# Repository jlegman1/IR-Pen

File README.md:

## Disclaimer
This project is intended for educational and research purposes only. It should be used responsibly and only in environments where you have permission to transmit infrared signals.
##
I created a PCB created that sends IR signals to TVs. You click a button and it uses TV-B-Gone firmware to cycle through all IR signals until a TV turns off. A custom 3d printed shell goes around it hiding the pcb. All kicad files and 3d print files linked. I had created this project because I was playing around with my flipper zero and thought how funny it was to when I turned the tv off when my dad was watching. It gave me motiavtion to create something of my own, so which i did. Overall I hope you enjoy playing around with my desgin!
PCB fits through my 3d printed shell and should fit there tightly but shouldn't fall out. Its diamater is 13mm and its 133mm in height. The PCB is 11mm x 65mm.
##
Firmware created by Mitch Altman and adafruit [TV-B-Gone](https://github.com/adafruit/TV-B-Gone-kit)
## Parts List

- **10440 Lithium Battery 3.7V** — power source that slides into pen body — [Amazon](https://www.amazon.com/dp/B0H1LNY5LW)
- **USBasp Programmer** — for flashing firmware via ISP pads — [Amazon](https://rb.gy/d68i6x)
- **Tactile Button** — trigger to fire IR codes — [DigiKey](https://www.digikey.com/en/products/detail/c-k/PTS526SM15SMTR2-LFS/10056625)
- **10µF Capacitor** — handles big voltage dips — [DigiKey](https://www.digikey.com/en/products/detail/murata-electronics/GRM155R60J106ME05D/11500166)
- **100nF Capacitor** — smooths out voltage spikes — [DigiKey](https://www.digikey.com/en/products/detail/murata-electronics/GRM155R61A104KA01D/587212?s=N4IgTCBcDaIOICUCyBGArGhA2FBBFADACwDSuBKAIiALoC%2BQA)
- **33Ω Resistor** — limits current to IR LED — [DigiKey](https://www.digikey.com/en/products/detail/yageo/RC0402JR-0733RL/726467)
- **3.3kΩ Resistor** — keeps charging at 300mA — [DigiKey](https://www.digikey.com/en/products/detail/panasonic-industry/ERA-2AEB332X/1706017)
- **10kΩ Resistors x2** — keeps ATtiny RESET and button pin stable — [DigiKey](https://www.digikey.com/en/products/detail/stackpole-electronics-inc/RMCF0402FT10K0/1761433)
- **USB-C Connector** — charges the battery — [DigiKey](https://www.digikey.com/en/products/detail/gct/USB4085-GF-A/9859662?s=N4IgTCBcDaIOIGEAqACAqgZQEIBYAMAHAKwgC6AvkA)
- **2N7002 MOSFET** — switch that drives the IR LED — [DigiKey](https://www.digikey.com/en/products/detail/onsemi/2N7002ET1G/1792136)
- **Keystone 5223** — battery spring contact — [DigiKey](https://www.digikey.com/en/products/detail/keystone-electronics/5223/316374)
- **TSAL6400** — IR LED — [DigiKey](https://www.digikey.com/en/products/detail/vishay-semiconductor-opto-division/TSAL6400/1681340)
- **MCP73831T** — battery charger IC — [DigiKey](https://www.digikey.com/en/products/detail/microchip-technology/MCP73831T-2ATI-OT/964303?s=N4IgTCBcDaILIGEAKB2AzADjQRgCoFowBBXASQHoB5XEAXQF8g)
- **ATtiny85-20SU** — main microcontroller — [DigiKey](https://www.digikey.com/en/products/detail/microchip-technology/ATTINY85-20SU/735470)
- Downloadable CSV up top
##

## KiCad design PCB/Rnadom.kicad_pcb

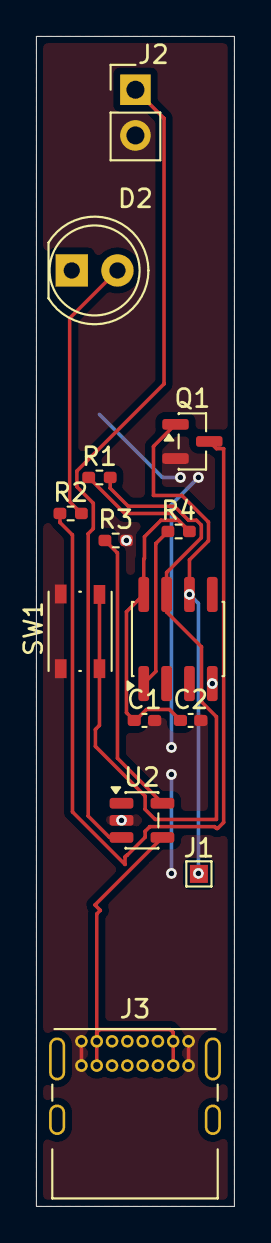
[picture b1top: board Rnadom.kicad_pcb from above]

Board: 2 copper layers, 11.0 x 65.0 mm, 14 parts (0 on the bottom side), 10 nets.

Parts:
C1: 100n; C_0402_1005Metric_Pad0.74x0.62mm_HandSolder
C2: 10u; C_0402_1005Metric_Pad0.74x0.62mm_HandSolder
D2: LED; LED_D5.0mm
J1: Conn_01x06; TestPoint_Pad_1.0x1.0mm
J2: Conn_01x02; PinHeader_1x02_P2.54mm_Vertical
J3: USB_C_Receptacle_USB2.0_14P; USB_C_Receptacle_GCT_USB4085
Q1: 2N7002; SOT-23
R1, R4: 10k; R_0402_1005Metric_Pad0.72x0.64mm_HandSolder
R2: 33; R_0402_1005Metric_Pad0.72x0.64mm_HandSolder
R3: 3.3k; R_0402_1005Metric_Pad0.72x0.64mm_HandSolder
SW1: SW_Push; SW_Push_1P1T_NO_Vertical_Wuerth_434133025816
U1: ATtiny85-20S; SOIC-8_3.9x4.9mm_P1.27mm
U2: MCP73831-2-OT; SOT-23-5

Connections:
/PB1: J1.1 (Pin_1_1), Q1.1 (G), U1.6 (PB1)
/PB2: R1.2, SW1.2, U1.7 (PB2)
/PB5: R4.1, U1.1 (~RESET/PB5)
/PROG: R3.1, U2.5 (PROG)
/VBAT: J2.1, U2.3 (V_{BAT})
/VBUS: J3.A4 (VBUS), J3.A9 (VBUS), J3.B4 (VBUS), J3.B9 (VBUS), U2.4 (V_{DD})
GND: C1.2, C2.2, J2.2, J3.A1 (GND), J3.A12 (GND), J3.B1 (GND), J3.B12 (GND), Q1.2 (S), R3.2, SW1.1, U1.4 (GND), U2.2 (V_{SS})
unnamed: D2.2 (A), R2.2
unnamed: Q1.3 (D), R2.1
VCC: C1.1, C2.1, R1.1, R4.2, U1.8 (VCC)

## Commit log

2026-05-26 README.md
2026-05-27 Update README to include firmware credit
    Added credit for firmware source in README.
2026-05-28 Fix typo in README for CSV download section
2026-06-12 Add Tv-B-Gone firmware file
2026-06-12 Create PCB files
2026-06-12 Create Kicad files
2026-06-13 Create IR pen shell
